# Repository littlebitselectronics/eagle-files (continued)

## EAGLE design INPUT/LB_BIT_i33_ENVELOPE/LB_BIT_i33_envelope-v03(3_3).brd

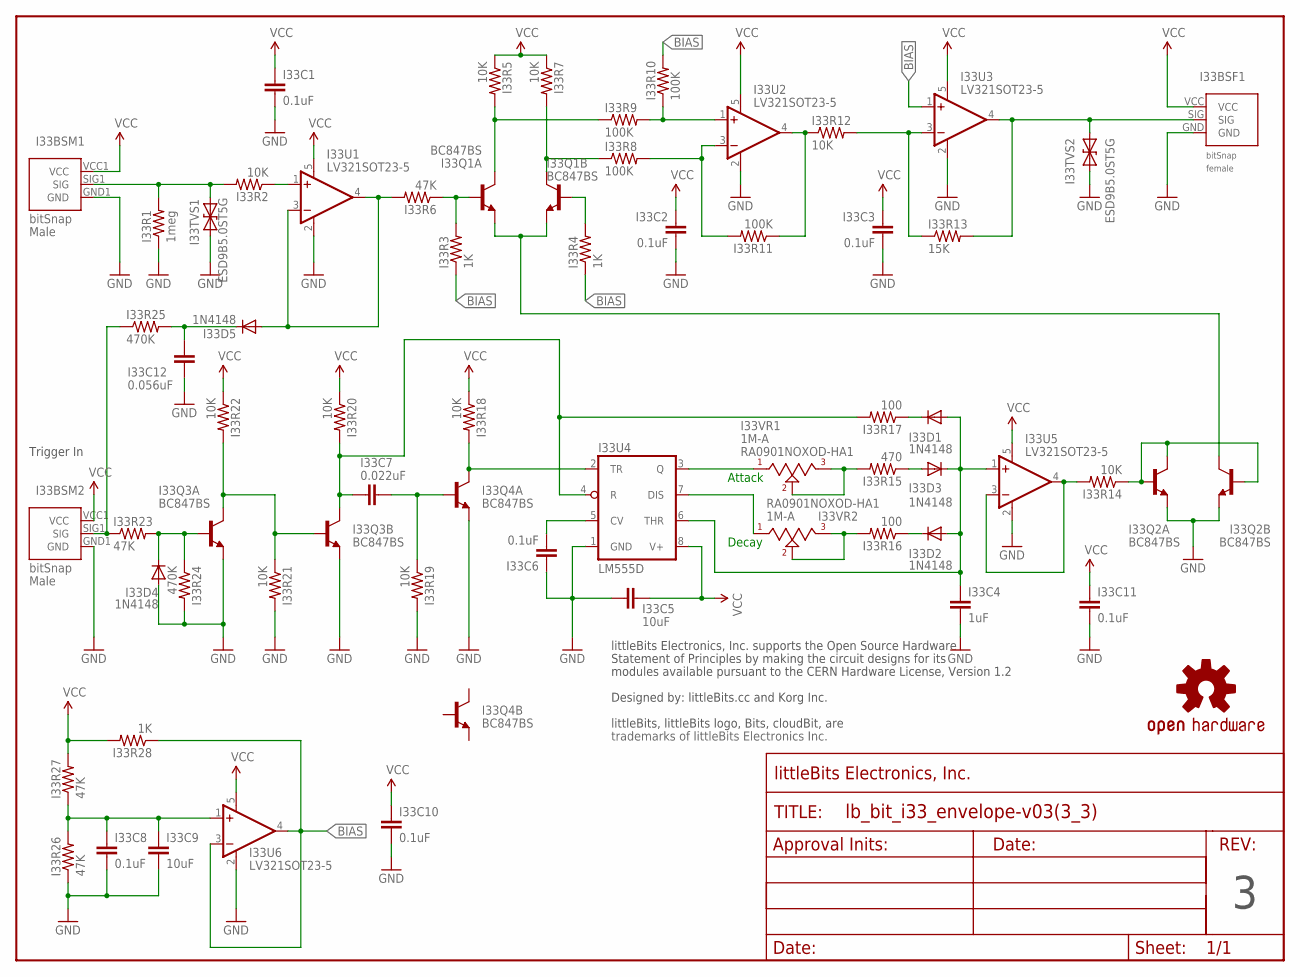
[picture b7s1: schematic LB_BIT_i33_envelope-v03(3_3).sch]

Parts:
I33BSF1: BITSNAP_V03_FEMALE
I33BSM1, I33BSM2: BITSNAP_V03_MALE
I33C1, I33C2, I33C3, I33C6, I33C8, I33C10, I33C11: 0.1uF; CAP-0603
I33C4: 1uF; CAP-0603
I33C5, I33C9: 10uF; CAP-0603
I33C7: 0.022uF; CAP-0603
I33C12: 0.056uF; CAP-0603
I33D1, I33D2, I33D3, I33D4, I33D5: 1N4148; SOD-323
I33Q1, I33Q2, I33Q3, I33Q4: BC847BS; SOT-363_PHILLIPS
I33R1: 1meg; RES-0603
I33R2, I33R5, I33R7, I33R12, I33R14, I33R18, I33R19, I33R20, I33R21, I33R22: 10K; RES-0603
I33R3, I33R4, I33R28: 1K; RES-0603
I33R6, I33R23, I33R26, I33R27: 47K; RES-0603
I33R8, I33R9, I33R10, I33R11: 100K; RES-0603
I33R13: 15K; RES-0603
I33R15: 470; RES-0603
I33R16, I33R17: 100; RES-0603
I33R24, I33R25: 470K; RES-0603
I33TVS1, I33TVS2: ESD9B5.0ST5G; SOD-923
I33U1, I33U2, I33U3, I33U5, I33U6: LV321SOT23-5; SOT23-5
I33U4: LM555D; SO08
I33VR1, I33VR2: 1M-A; ALPS_POT
U$1: FRAME-LETTER-OHWOHW; FABDWG01-OHW
U$3: OSHWCREDIT-KORG
U$9: OSHW-LOGOL; OSHW-LOGO-L

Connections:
BIAS: I33R3.1, I33R4.1, I33R10.2, I33R28.1, I33U3.1 (+IN), I33U6.3 (-IN), I33U6.4 (OUT)
GND: I33BSF1.GND, I33BSM1.GND1 (GND), I33BSM2.GND1 (GND), I33C1.2, I33C2.2, I33C3.2, I33C4.2, I33C5.1, I33C6.1, I33C8.2, I33C9.2, I33C10.2, I33C11.2, I33C12.2, I33D4.2 (A), I33Q2.1 (E), I33Q2.4 (E), I33Q3.1 (E), I33Q3.4 (E), I33Q4.1 (E), I33R1.1, I33R19.2, I33R21.2, I33R24.2, I33R26.1, I33TVS1.1 (A), I33TVS2.1 (A), I33U1.2 (V-), I33U2.2 (V-), I33U3.2 (V-), I33U4.1 (GND), I33U5.2 (V-), I33U6.2 (V-)
unnamed: I33Q1.2 (B), I33R3.2, I33R6.1
unnamed: I33D5.2 (A), I33R6.2, I33U1.3 (-IN), I33U1.4 (OUT)
unnamed: I33Q2.2 (B), I33Q2.5 (B), I33Q2.6 (C), I33R14.1
unnamed: I33R2.1, I33U1.1 (+IN)
unnamed: I33Q1.6 (C), I33R5.2, I33R9.1
unnamed: I33Q1.3 (C), I33R7.2, I33R8.1
unnamed: I33Q1.1 (E), I33Q1.4 (E), I33Q2.3 (C)
unnamed: I33Q1.5 (B), I33R4.2
unnamed: I33R9.2, I33R10.1, I33U2.1 (+IN)
unnamed: I33R8.2, I33R11.2, I33U2.3 (-IN)
unnamed: I33R11.1, I33R12.1, I33U2.4 (OUT)
unnamed: I33R12.2, I33R13.1, I33U3.3 (-IN)
unnamed: I33Q3.5 (B), I33Q3.6 (C), I33R21.1, I33R22.2
unnamed: I33R14.2, I33U5.3 (-IN), I33U5.4 (OUT)
unnamed: I33C7.2, I33Q3.3 (C), I33R17.2, I33R20.2, I33U4.4 (R)
unnamed: I33C4.1, I33D1.2 (A), I33D2.2 (A), I33D3.1 (C), I33U4.6 (THR), I33U5.1 (+IN)
unnamed: I33D3.2 (A), I33R15.1
unnamed: I33R15.2, I33VR1.2, I33VR1.3
unnamed: I33D2.1 (C), I33R16.1
unnamed: I33R16.2, I33VR2.2, I33VR2.3
unnamed: I33D1.1 (C), I33R17.1
unnamed: I33C7.1, I33Q4.2 (B), I33R19.1
unnamed: I33U4.7 (DIS), I33VR2.1
unnamed: I33U4.3 (Q), I33VR1.1
unnamed: I33BSM2.SIG1 (SIG), I33R23.1, I33R25.1
unnamed: I33C6.2, I33U4.5 (CV)
unnamed: I33D4.1 (C), I33Q3.2 (B), I33R23.2, I33R24.1
unnamed: I33C8.1, I33C9.1, I33R26.2, I33R27.1, I33U6.1 (+IN)
unnamed: I33Q4.6 (C), I33R18.2, I33U4.2 (TR)
unnamed: I33C12.1, I33D5.1 (C), I33R25.2
SIG_IN: I33BSM1.SIG1 (SIG), I33R1.2, I33R2.2, I33TVS1.2 (C)
SIG_OUT: I33BSF1.SIG, I33R13.2, I33TVS2.2 (C), I33U3.4 (OUT)
VCC: I33BSF1.VCC, I33BSM1.VCC1 (VCC), I33BSM2.VCC1 (VCC), I33C1.1, I33C2.1, I33C3.1, I33C5.2, I33C10.1, I33C11.1, I33R5.1, I33R7.1, I33R18.1, I33R20.1, I33R22.1, I33R27.2, I33R28.2, I33U1.5 (V+), I33U2.5 (V+), I33U3.5 (V+), I33U4.8 (V+), I33U5.5 (V+), I33U6.5 (V+)

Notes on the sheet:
Decay
Attack
Trigger In
RA0901NOXOD-HA1

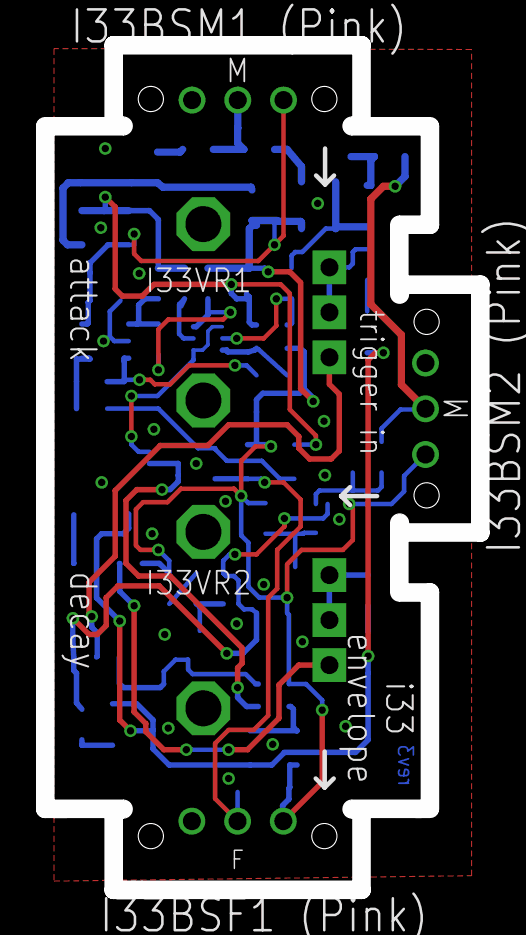
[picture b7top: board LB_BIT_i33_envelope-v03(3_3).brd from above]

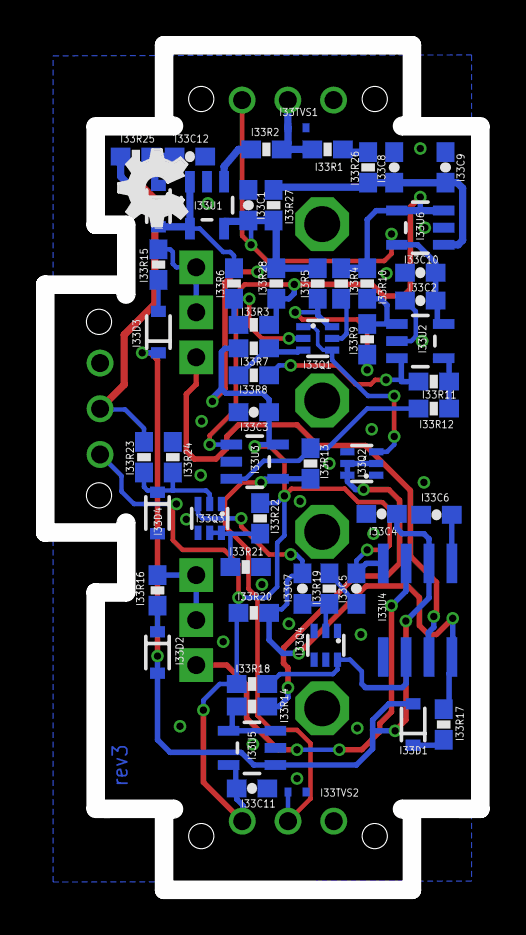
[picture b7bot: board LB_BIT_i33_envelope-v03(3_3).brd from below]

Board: 2 copper layers, 24.2 x 46.9 mm, 66 parts (57 on the bottom side), 35 nets.

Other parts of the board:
U$8: OSHW_FILLX150_NOTEXT

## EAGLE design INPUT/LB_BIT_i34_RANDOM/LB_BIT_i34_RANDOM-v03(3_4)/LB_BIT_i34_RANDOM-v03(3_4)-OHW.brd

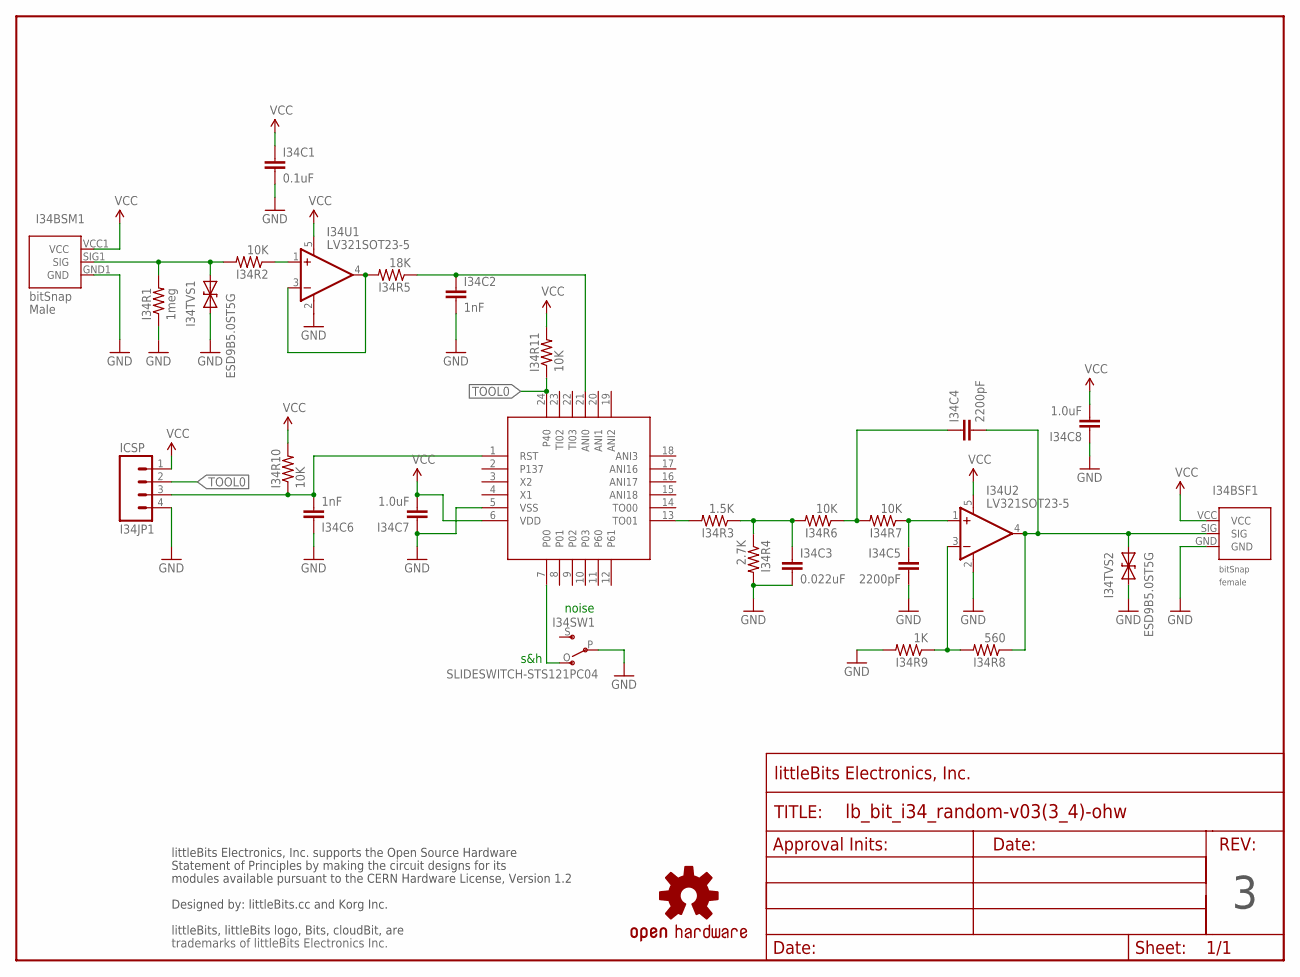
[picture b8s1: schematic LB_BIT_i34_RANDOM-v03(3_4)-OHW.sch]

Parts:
I34BSF1: BITSNAP_V03_FEMALE
I34BSM1: BITSNAP_V03_MALE
I34C1: 0.1uF; CAP-0603
I34C2, I34C6: 1nF; CAP-0603
I34C3: 0.022uF; CAP-0603
I34C4, I34C5: 2200pF; CAP-0603
I34C7, I34C8: 1.0uF; CAP-0603
I34JP1: ICSP; SIP4-SM-0.1IN-NOS.S.
I34R1: 1meg; RES-0603
I34R2, I34R6, I34R7, I34R10, I34R11: 10K; RES-0603
I34R3: 1.5K; RES-0603
I34R4: 2.7K; RES-0603
I34R5: 18K; RES-0603
I34R8: 560; RES-0603
I34R9: 1K; RES-0603
I34SW1: SLIDESWITCH-STS121PC04
I34TVS1, I34TVS2: ESD9B5.0ST5G; SOD-923
I34U1, I34U2: LV321SOT23-5; SOT23-5
I34U3: R5F10278QFN-24; QFN-24(4MM)
U$1: FRAME-LETTER-OHWOHW; FABDWG01-OHW
U$2: OSHWCREDIT-KORG
U$3: OSHW-LOGOL; OSHW-LOGO-L

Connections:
GND: I34BSF1.GND, I34BSM1.GND1 (GND), I34C1.2, I34C2.2, I34C3.2, I34C5.2, I34C6.1, I34C7.1, I34C8.1, I34JP1.4, I34R1.1, I34R4.2, I34R9.2, I34SW1.P, I34TVS1.1 (A), I34TVS2.1 (A), I34U1.2 (V-), I34U2.2 (V-), I34U3.5 (VSS)
unnamed: I34C2.1, I34R5.1, I34U3.21 (ANI0)
unnamed: I34R5.2, I34U1.3 (-IN), I34U1.4 (OUT)
unnamed: I34C3.1, I34R3.1, I34R4.1, I34R6.2
unnamed: I34R2.1, I34U1.1 (+IN)
unnamed: I34R3.2, I34U3.13 (TO01)
unnamed: I34R8.2, I34R9.1, I34U2.3 (-IN)
unnamed: I34C4.1, I34R6.1, I34R7.2
unnamed: I34C6.2, I34JP1.3, I34R10.1, I34U3.1 (RST)
unnamed: I34C5.1, I34R7.1, I34U2.1 (+IN)
unnamed: I34SW1.O, I34U3.7 (P00)
SIG_IN: I34BSM1.SIG1 (SIG), I34R1.2, I34R2.2, I34TVS1.2 (C)
SIG_OUT: I34BSF1.SIG, I34C4.2, I34R8.1, I34TVS2.2 (C), I34U2.4 (OUT)
TOOL0: I34JP1.2, I34R11.1, I34U3.24 (P40)
VCC: I34BSF1.VCC, I34BSM1.VCC1 (VCC), I34C1.1, I34C7.2, I34C8.2, I34JP1.1, I34R10.2, I34R11.2, I34U1.5 (V+), I34U2.5 (V+), I34U3.6 (VDD)

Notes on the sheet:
noise
s&h

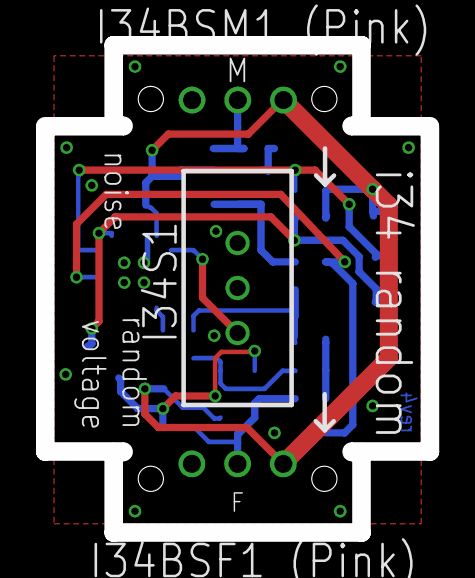
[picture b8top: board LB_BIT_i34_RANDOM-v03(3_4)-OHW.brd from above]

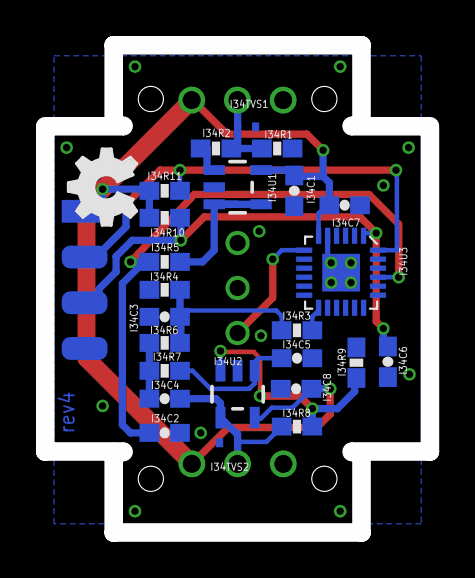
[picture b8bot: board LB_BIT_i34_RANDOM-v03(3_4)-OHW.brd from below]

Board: 2 copper layers, 21.4 x 27.1 mm, 32 parts (25 on the bottom side), 15 nets.

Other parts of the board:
U$4: OSHW_FILLX150_NOTEXT

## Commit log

2012-01-12 Initial commit
    Adds boards and schematics for starter kit v0.2
2012-01-12 Add README and LICENSE
2012-01-12 Fix broken link in README
2012-01-12 Add title to LICENSE
2012-03-28 Added new Bits and updated Starter Kit file names
    Added new Bits (toggle switch, slide dimmer, temp sensor, light
    trigger, motion trigger, roller switch, long led, dc motor, fan, coin
    battery, usb power, branch).
    Updated Starter Kit file names with version and revision number.
2012-03-29 new Bit added
    new Bit added (light sensor)
2012-04-03 Corrected a small typo
2012-04-12 Added PDFs of all module schematics
2012-04-18 Updated P1-Power bit
2012-06-20 Added schematic PDFs
    for double AND, double OR, uv led, and slide switch
2012-06-27 Added o6-Buzzer
    Added o6-Buzzer schematic and board file
2012-11-06 Removed littlebits Logos in many of these
2012-11-07 cLeared off more littleBits logos
2013-09-04 Added motion trigger v03(rev3_2) and slide dimmer
2013-09-04 Added slide dimmer, motion trigger, and light trigger updates.
2013-09-05 put all existing eagle files and pdfs into organized folders
2013-09-05 added all new eagle files for INPUT bits
2013-09-05 removed new LIGHTTRIGGER since its not in production, per Paul's instructions
2013-09-05 added BENDSENSOR, TIMEOUT, SOUNDTRIGGER
2013-09-05 added FORK and INVERTER
2013-09-05 added all missing eagle files for new versions WIRE bits
2013-09-05 added all new versions of POWER bits
2013-09-05 added all new eagle files for OUTPUT bits
2013-09-05 fixed mirrored OHW servo pdf
2013-09-05 fixed mirrored OHW brightLED pdf
2013-09-05 fixed mirrored lightwire pdf
2013-09-05 fixed mirrored OHW USBPower pdf
2013-09-05 fixed ground plane on OHW BRD
2013-11-25 Update README.md
    Updated OSHW statement
2013-12-06 Added Oscillator.
2013-12-06 UPdated PDF
2013-12-06 Added keyboard files.
2013-12-09 Added microsequencer files.
2013-12-09 Added envelope files.
2013-12-09 Added "main" and "in" MIX files.
2013-12-09 Added Delay files.
2013-12-09 Added split files.
2013-12-09 Added random files.
2013-12-09 Added OHW files.
2013-12-09 Added synth speaker files.
2014-03-10 Updated Long LED schematic PDF.
2014-03-18 Changed LICENSE to the CERN Open Hardware License
    You have listed on README.md that you use the CERN Open Hardware license v1.2, so I am changing this file to match that license.
2014-08-01 Updated Split folder title.
    Uploaded cloudv1 files.
2014-08-01 Updated Split folder to say LB_BIT
2014-08-01 Added Arduino files.
2014-08-01 Updated address and license.
2014-08-01 Updated license.
2014-08-01 Updated PDFs
2014-08-04 Updated licenses
2014-08-06 Merged Arduino schematic pdfs into a single document
2014-08-20 Added Wireless Receiver, Wireless Transmitter, NOR, NAND, and XOR SCH and BRD files
2014-08-22 Added PDFs of schematics
2014-08-22 Added SCH, BRD, and PDF files for microphone, sequencer, number, and latch modules.
2014-08-26 Updated license text
2014-08-26 Updated license in Korg bits modules
